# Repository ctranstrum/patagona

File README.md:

# Patagona Keyboards

Compact wireless ergo keyboards built around the [XIAO BLE][xiao] microcontroller
and running [ZMK][zmk] firmware with full [ZMK Studio][studio] support.
Named after the two species of giant hummingbird — the largest hummingbirds in the world.

## Features

- **Wireless** — internal LiPo battery; no cables required day to day
- **Live remapping** — ZMK Studio lets you customize your keymap over USB without recompiling firmware
- **Hotswap** — Kailh Choc sockets support both v1 and v2 switches; swap anytime
- **3D-printed case** — printable at home on any FDM printer, with split versions for smaller beds
- **Open hardware** — all source files included, licensed under [CERN-OHL-P-2.0][ohl]

## Patagona gigas

30–32 keys with a five-way joystick switch at the center,
within reach of either thumb for scroll, navigation, or mouse control.

[Build guide](BUILD-gigas.md) · [Printable case files][case-gigas] · [Firmware][firmware]

## Patagona chaski

40–42 keys for those who want the 3x6 layout and more thumb keys.

[Build guide](BUILD-chaski.md) · [Printable case files][case-chaski] · [Firmware][firmware]

## Heritage

The [Patagona genus][patagona-wiki] is home to the two largest hummingbirds in the world.
_P. gigas_ is the migratory giant, ascending over 4,000 meters and traveling more than
4,000 km each way between the Chilean coast and the Peruvian Andes each year.
_P. chaski_ is its slightly larger but sedentary cousin.

These keyboards follow in the tradition of the original [Hummingbird design][pje66],
which used a XIAO SAMD21 and topped out at 30 keys
due to the maximum capacity of the 5×6 matrix allowed by the 11 pins on that board.
The Patagona boards use the XIAO BLE, whose NFC pads can be repurposed as GPIO —
adding two extra pins, enabling a 6×7 matrix and up to 42 keys.

[case-gigas]: https://github.com/ctranstrum/patagona/tree/main/cases/gigas#readme
[case-chaski]: https://github.com/ctranstrum/patagona/tree/main/cases/chaski#readme
[firmware]: https://github.com/ctranstrum/patagona-zmk
[ohl]: LICENSE.txt
[patagona-wiki]: https://en.wikipedia.org/wiki/Giant_hummingbird
[pje66]: https://github.com/PJE66/hummingbird
[studio]: https://zmk.dev/docs/features/studio
[xiao]: https://wiki.seeedstudio.com/XIAO_BLE/
[zmk]: https://zmk.dev

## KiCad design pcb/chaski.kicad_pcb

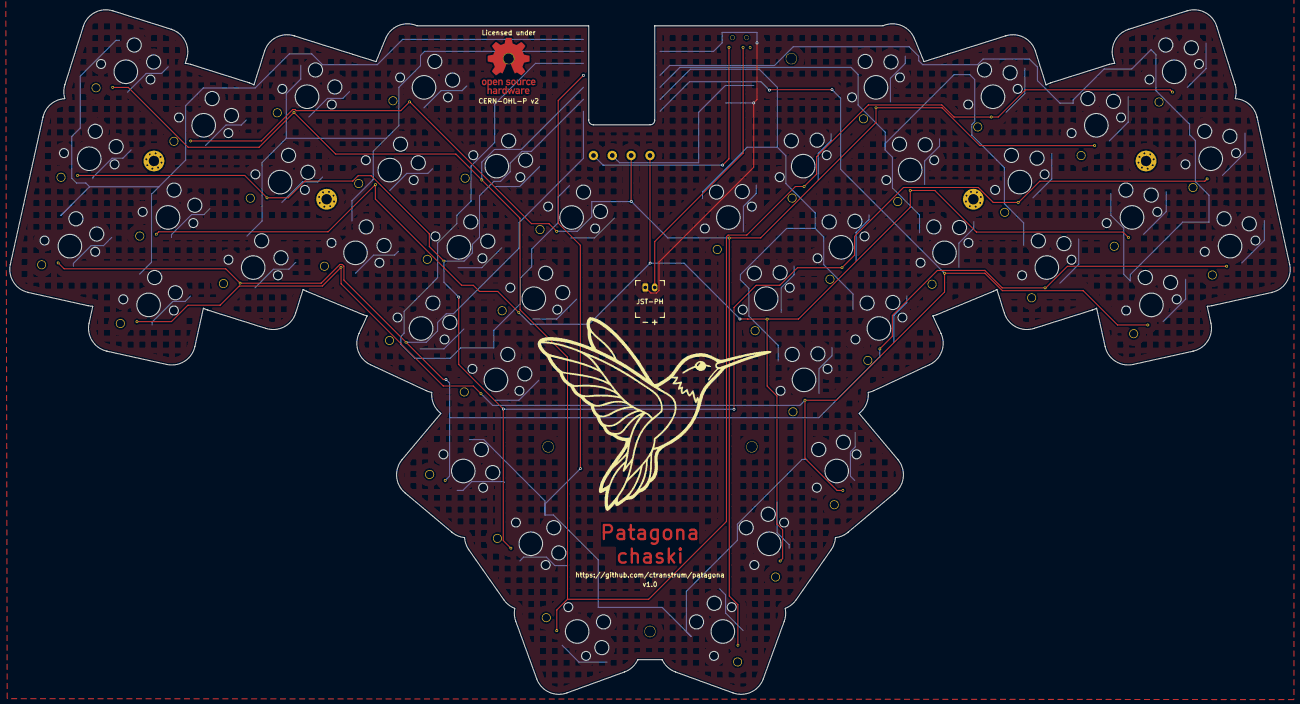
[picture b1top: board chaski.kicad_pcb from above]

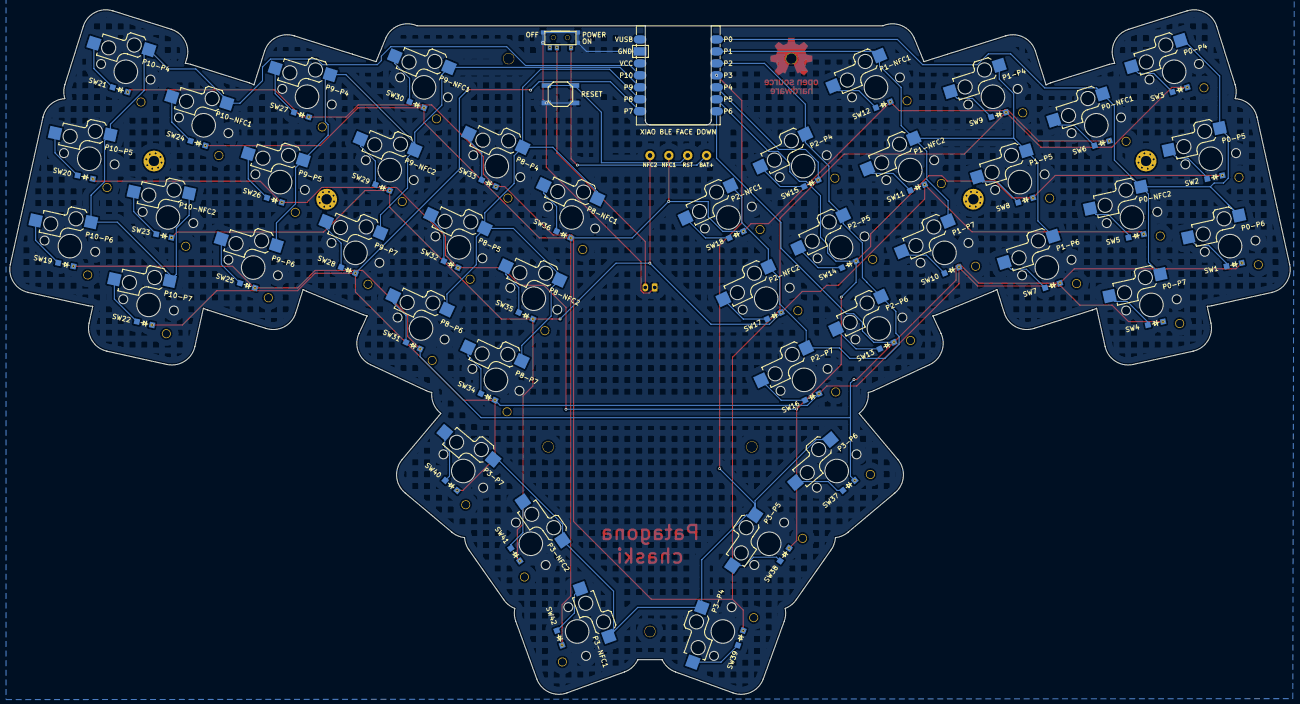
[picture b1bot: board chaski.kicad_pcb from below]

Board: 2 copper layers, 271.7 x 145.2 mm, 93 parts (85 on the bottom side), 59 nets.

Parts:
JST1: battery_connector_jst_ph_2
MCU1: xiao-ble
PAD1, PAD2, PAD3, PAD4: SMDPad
PG**: p-gigas
S1, S2, S3, S4, S5, S6, S7, S8, S9, S10, S11, S12, S13, S14, S15, S16, S17, S18, S19, S20, S21, S22, S23, S24, S25, S26, S27, S28, S29, S30, S31, S32, S33, S34, S35, S36, S37, S38, S39, S40, S41, S42: switch_choc_v1_v2
SW1, SW2, SW3, SW4, SW5, SW6, SW7, SW8, SW9, SW10, SW11, SW12, SW13, SW14, SW15, SW16, SW17, SW18, SW19, SW20, SW21, SW22, SW23, SW24, SW25, SW26, SW27, SW28, SW29, SW30, SW31, SW32, SW33, SW34, SW35, SW36, SW37, SW38, SW39, SW40, SW41, SW42: ComboDiode
SW43: pts526
T1: SPDT_C128955

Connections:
BAT+: PAD1.1, T1.1
GND: JST1.1, MCU1.13, SW43.1
NFC1: PAD3.1, SW6.1, SW12.1, SW18.1, SW24.1, SW30.1, SW36.1, SW42.1
NFC2: PAD4.1, SW5.1, SW11.1, SW17.1, SW23.1, SW29.1, SW35.1, SW41.1
P0: MCU1.1, S1.1, S2.1, S3.1, S4.1, S5.1, S6.1
P1: MCU1.2, S7.1, S8.1, S9.1, S10.1, S11.1, S12.1
P2: MCU1.3, S13.1, S14.1, S15.1, S16.1, S17.1, S18.1
P3: MCU1.4, S37.1, S38.1, S39.1, S40.1, S41.1, S42.1
P4: MCU1.5, SW3.1, SW9.1, SW15.1, SW21.1, SW27.1, SW33.1, SW39.1
P5: MCU1.6, SW2.1, SW8.1, SW14.1, SW20.1, SW26.1, SW32.1, SW38.1
P6: MCU1.7, SW1.1, SW7.1, SW13.1, SW19.1, SW25.1, SW31.1, SW37.1
P7: MCU1.8, SW4.1, SW10.1, SW16.1, SW22.1, SW28.1, SW34.1, SW40.1
P8: MCU1.9, S31.1, S32.1, S33.1, S34.1, S35.1, S36.1
P9: MCU1.10, S25.1, S26.1, S27.1, S28.1, S29.1, S30.1
P10: MCU1.11, S19.1, S20.1, S21.1, S22.1, S23.1, S24.1
RAW: JST1.2, T1.2
RST: PAD2.1, SW43.2
index_bottom: S13.2, SW13.2
index_home: S14.2, SW14.2
index_top: S15.2, SW15.2
inner_bottom: S16.2, SW16.2
inner_home: S17.2, SW17.2
inner_top: S18.2, SW18.2
middle_bottom: S10.2, SW10.2
middle_home: S11.2, SW11.2
middle_top: S12.2, SW12.2
mirror_index_bottom: S31.2, SW31.2
mirror_index_home: S32.2, SW32.2
mirror_index_top: S33.2, SW33.2
mirror_inner_bottom: S34.2, SW34.2
mirror_inner_home: S35.2, SW35.2
mirror_inner_top: S36.2, SW36.2
mirror_middle_bottom: S28.2, SW28.2
mirror_middle_home: S29.2, SW29.2
mirror_middle_top: S30.2, SW30.2
mirror_outer_bottom: S19.2, SW19.2
mirror_outer_home: S20.2, SW20.2
mirror_outer_top: S21.2, SW21.2
mirror_pinky_bottom: S22.2, SW22.2
mirror_pinky_home: S23.2, SW23.2
mirror_pinky_top: S24.2, SW24.2
mirror_primary_spot: S41.2, SW41.2
mirror_reachy_spot: S42.2, SW42.2
mirror_ring_bottom: S25.2, SW25.2
mirror_ring_home: S26.2, SW26.2
mirror_ring_top: S27.2, SW27.2
mirror_secondary_spot: S40.2, SW40.2
outer_bottom: S1.2, SW1.2
outer_home: S2.2, SW2.2
outer_top: S3.2, SW3.2
pinky_bottom: S4.2, SW4.2
pinky_home: S5.2, SW5.2
pinky_top: S6.2, SW6.2
primary_spot: S38.2, SW38.2
reachy_spot: S39.2, SW39.2
ring_bottom: S7.2, SW7.2
ring_home: S8.2, SW8.2
ring_top: S9.2, SW9.2
secondary_spot: S37.2, SW37.2

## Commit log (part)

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2026-05-12 add hummingbird images
2026-05-13 gigas ready
2026-05-17 chaski pcb ready
2026-05-18 chaski gerbers
2026-05-19 cases
2026-05-20 resolve merge conflicts on gitignore
2026-05-21 fix p chaski cases
2026-05-28 add joystick
2026-05-30 fix tolerances for 5-way switch cap
2026-06-03 refine case files for p gigas
2026-06-03 add joystick stl file
2026-06-06 reduce precision in stl files
2026-06-06 use dynamic segments
2026-06-17 fix: NFC1 and NFC2 were mis-labeled on the PCB

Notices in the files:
pcb/chaski.kicad_pcb:
CERN-OHL-P v2
